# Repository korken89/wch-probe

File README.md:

# wch-probe

KiCad hardware for a CH347F-based JTAG & SWD debug probe. USB-C on one end, a
10-pin 1.27 mm Cortex debug header on the other, plus a UART on the bottom-side
TX/RX/GND pads. The I/O voltage (VIO) tracks the target's VTref (valid range
1.8 V to 3.3 V), and defaults to 3.3 V when the target does not drive VTref.

## Fabrication

The fabrication outputs (gerber zip, BOM, placement file, schematic PDF) for
each board revision are attached to the
[releases](https://github.com/korken89/wch-probe/releases). To generate them
locally, `make fab` writes the same set to `Fabrication/` and `make check`
runs ERC and DRC; both need KiCad 10's `kicad-cli`.

## Ordering

JLCPCB, 4 layers, 1.6 mm thick. Order options:

- Stackup: JLC04161H-7628 with impedance control (the USB pair is 90 ohm
  differential)
- Surface finish: HASL lead-free

## USB identity

Stock CH347s ship with a blank config and all enumerate with the same default serial.
Use [wch-cfg](https://github.com/korken89/wch-cfg) to write each board's USB identity
(serial number, product and manufacturer strings):

```sh
wch-cfg version --min 1.01 && wch-cfg write --init --random-serial --product wch-probe --manufacturer korken89
# replug the board (the chip reads the strings at power-on), then
wch-cfg verify --serial <the printed serial> --product wch-probe --manufacturer korken89
```

`write` prints the serial for the label on stdout once the OS has enumerated it.

## Gotchas

### Several probes behind one hub can fail to enumerate.

The CH347 declares its interrupt endpoints with 125/250 us polling, and the
host controller reserves that bandwidth at enumeration whether the endpoints
are used or not. After a few probes it will error with `can't set config #1,
error -28` ("Not enough bandwidth"). Work around it on Linux by treating
the `bInterval` values as milliseconds (will support 8x more probes - UART,
JTAG and SWD run on bulk endpoints and are unaffected):

```sh
echo '1a86:55de:l' | sudo tee /sys/module/usbcore/parameters/quirks
```

then replug the probes (quirks apply at enumeration). To make it permanent,
add `usbcore.quirks=1a86:55de:l` to the kernel command line. `dmesg` printing
`endpoint 0x85 has an invalid bInterval 1, changing to 4` for each probe
confirms the quirk is active.

## License

CERN-OHL-P-2.0, see [LICENSE](LICENSE).

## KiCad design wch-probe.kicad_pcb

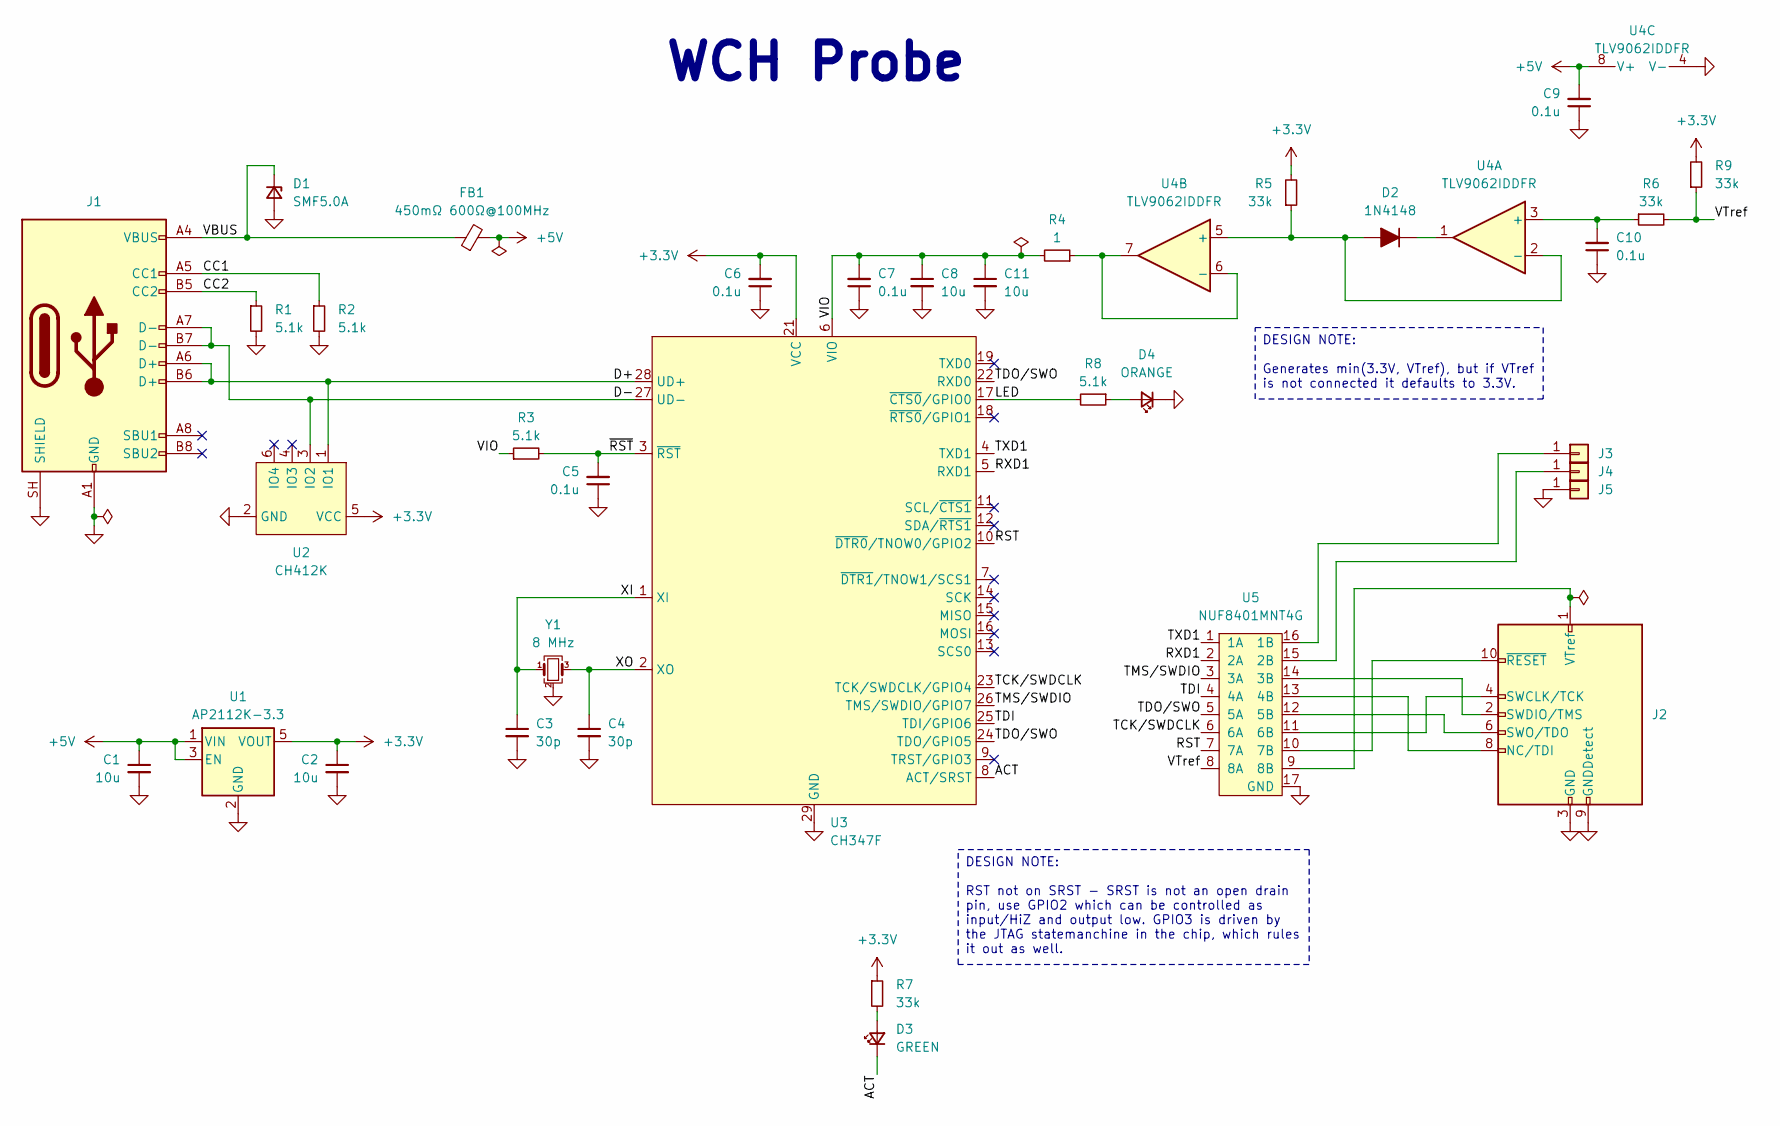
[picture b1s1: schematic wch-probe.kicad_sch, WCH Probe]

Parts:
C1, C2, C8, C11: 10u; C_0603; LCSC C96446
C3, C4: 30p; C_0402; LCSC C1570
C5, C6, C7, C9, C10: 0.1u; C_0402; LCSC C1525
D1: SMF5.0A; D_SOD-123F; LCSC C151296
D2: 1N4148; D_SOD-523; LCSC C83482
D3: GREEN; LED_0402_1005Metric; LCSC C5123485
D4: ORANGE; LED_0402_1005Metric; LCSC C965791
FB1: 450mΩ 600Ω@100MHz; R_0603; LCSC C1002
J1: USB_C_Receptacle_USB2.0_14P; USB_C_Receptacle_GCT_USB4105-xx-A_16P_TopMnt_Horizontal; LCSC C165948
J2: Conn_ARM_JTAG_SWD_10; PinHeader_2x05_FTSH-105-01-L-DV-K; LCSC C5155080
J3, J4, J5: Conn_01x01; pad_1.5x2.5mm
R1, R2, R3, R8: 5.1k; R_0402; LCSC C25905
R4: 1; R_0402; LCSC C25086
R5, R6, R7, R9: 33k; R_0402; LCSC C25779
U1: AP2112K-3.3; SOT-23-5; LCSC C23380830
U2: CH412K; SOT-363_SC-70-6; LCSC C89184
U3: CH347F; WQFN-28-1EP_4x4mm_P0.4mm_EP2.7x2.7mm; LCSC C18221627
U4: TLV9062IDDFR; SOT-23-8; LCSC C2867884
U5: NUF8401MNT4G; DFN-16-1EP_1.6x4mm_P0.5mm; LCSC C895158
Y1: 8 MHz; Crystal_SMD_3225-4Pin_3.2x2.5mm; LCSC C5563850

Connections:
+3.3V: C2.1, C6.2, R5.2, R7.1, R9.2, U1.5 (VOUT), U2.5 (VCC), U3.21 (VCC)
+5V: C1.1, C9.2, FB1.2, U1.1 (VIN), U1.3 (EN), U4.8 (V+)
/ACT: D3.1 (K), U3.8 (ACT/SRST)
/CC1: J1.A5 (CC1), R2.1
/CC2: J1.B5 (CC2), R1.1
/D+: J1.A6 (D+), J1.B6 (D+), U2.1 (IO1), U3.28 (UD+)
/D-: J1.A7 (D-), J1.B7 (D-), U2.3 (IO2), U3.27 (UD-)
/LED: R8.2, U3.17 (~CTS0/GPIO0)
/RST: U3.10 (~DTR0/TNOW0/GPIO2), U5.7 (7A)
/RXD1: U3.5 (RXD1), U5.2 (2A)
/TCK/SWDCLK: U3.23 (TCK/SWDCLK/GPIO4), U5.6 (6A)
/TDI: U3.25 (TDI/GPIO6), U5.4 (4A)
/TDO/SWO: U3.22 (RXD0), U3.24 (TDO/GPIO5), U5.5 (5A)
/TMS/SWDIO: U3.26 (TMS/SWDIO/GPIO7), U5.3 (3A)
/TXD1: U3.4 (TXD1), U5.1 (1A)
/VBUS: D1.1 (K), FB1.1, J1.A4 (VBUS), J1.A9 (VBUS), J1.B4 (VBUS), J1.B9 (VBUS)
/VIO: C7.2, C8.1, C11.1, R3.1, R4.2, U3.6 (VIO)
/VTref: R6.2, R9.1, U5.8 (8A)
/XI: C3.1, U3.1 (XI), Y1.1
/XO: C4.1, U3.2 (XO), Y1.3
/~RST: C5.2, R3.2, U3.3 (~RST)
GND: C1.2, C2.2, C3.2, C4.2, C5.1, C6.1, C7.1, C8.2, C9.1, C10.1, C11.2, D1.2 (A), D4.1 (K), J1.A1 (GND), J1.A12 (GND), J1.B1 (GND), J1.B12 (GND), J1.SH (SHIELD), J2.3 (GND), J2.5 (GND), J2.9 (GNDDetect), J5.1 (Pin_1_1), R1.2, R2.2, U1.2 (GND), U2.2 (GND), U3.20 (GND), U3.29 (GND), U4.4 (V-), U5.17 (GND), Y1.2 (G), Y1.4 (G)
unnamed: D2.2 (A), R5.1, U4.2 (-), U4.5 (+)
unnamed: D2.1 (K), U4.1
unnamed: D3.2 (A), R7.2
unnamed: D4.2 (A), R8.1
unnamed: J2.8 (NC/TDI), U5.13 (4B)
unnamed: J2.4 (SWCLK/TCK), U5.11 (6B)
unnamed: J2.2 (SWDIO/TMS), U5.14 (3B)
unnamed: J2.6 (SWO/TDO), U5.12 (5B)
unnamed: J2.1 (VTref), U5.9 (8B)
unnamed: J2.10 (~RESET), U5.10 (7B)
unnamed: J3.1 (Pin_1_1), U5.16 (1B)
unnamed: J4.1 (Pin_1_1), U5.15 (2B)
unnamed: C10.2, R6.1, U4.3 (+)
unnamed: R4.1, U4.6 (-), U4.7

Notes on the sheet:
WCH Probe
DESIGN NOTE: RST not on SRST - SRST is not an open drain pin, use GPIO2 which can be controlled as input/HiZ and output low. GPIO3 is driven by the JTAG statemanchine in the chip, which rules it out as well.
DESIGN NOTE: Generates min(3.3V, VTref), but if VTref is not connected it defaults to 3.3V.

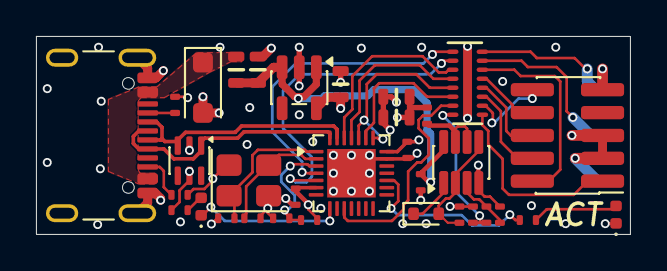
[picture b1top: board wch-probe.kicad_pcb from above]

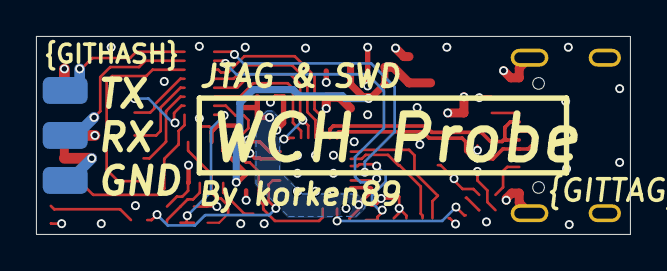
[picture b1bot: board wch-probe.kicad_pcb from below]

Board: 4 copper layers, 33.0 x 11.0 mm, 36 parts (3 on the bottom side), 36 nets.
